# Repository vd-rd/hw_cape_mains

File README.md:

## Overview
 Isolated mains supply module designed to power IoT projects that have a <15W power requirement. It is designed around readily available step-down power modules with additional filtering to ensure compliance to standard specifications.

### Specifications

Two versions of the board are available, depending on the choice of the module:
 * MeanWell IRM 
 * Aimtec AMEOF 

In both cases the boards feature:
 * 85-240V input
 * 15W output at 12V
 * 5V regulated output using an LDO
 * Current sensor for measuring board consumption
 * IEC-C6 power connector
The board has a small footprint (80x40x25mm) with the power connector protruding an additional 3mm at the edge.

### Resources
You can find all necesary information to build or evaluate the module here:
   - [View layout and schematic](https://cadlab.io/project/) 
   - [View 3D board render](https://a360.co/2V6xbaF)
   - [Fabrication files](https://github.com/vd-rd/hw_cape_mains/releases)

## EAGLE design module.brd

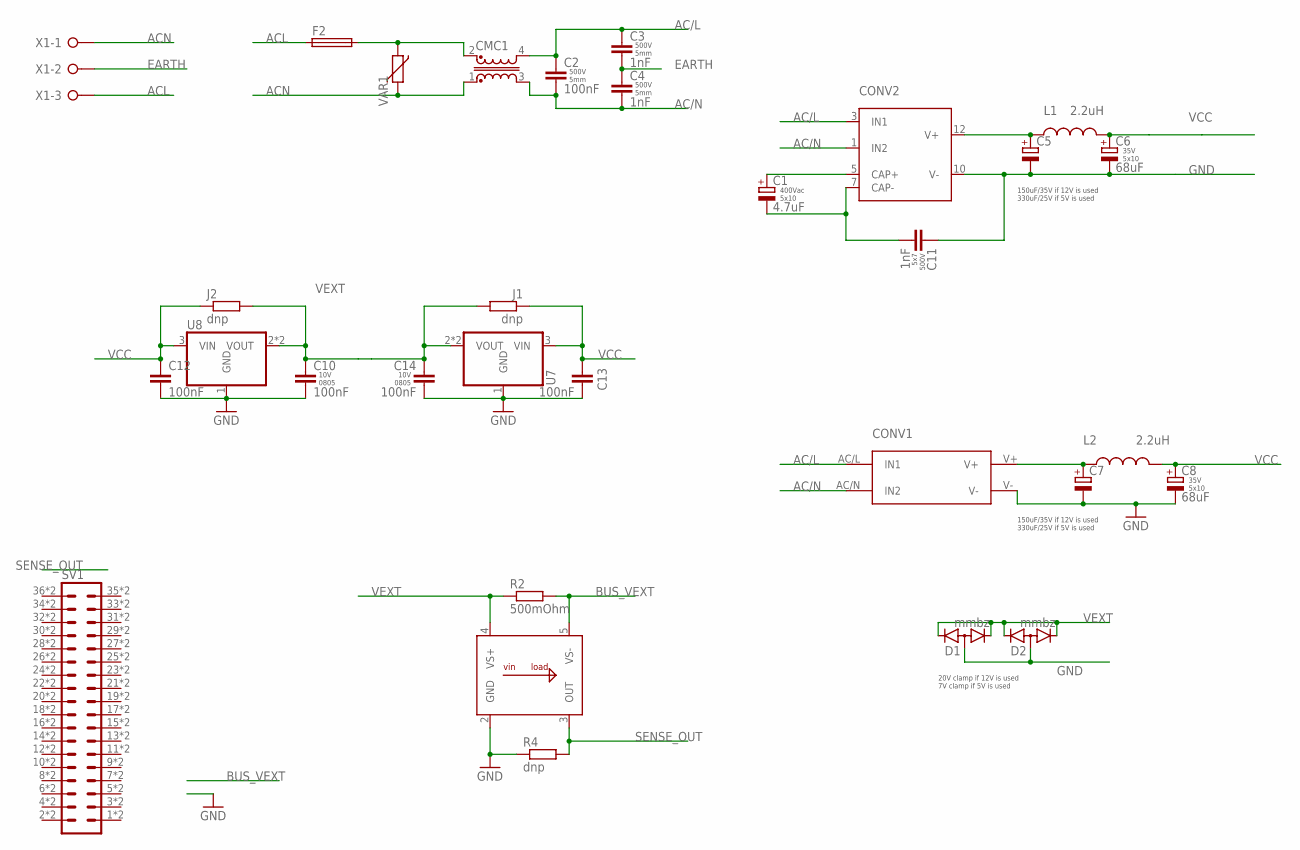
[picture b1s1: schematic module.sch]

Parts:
C1: 4.7uF; CAPPRD508W65D1000H1600B; RATING 400Vac
C2: 100nF; C050-025X075; RATING 500V
C3, C4: 1nF; C050-025X075; RATING 500V
C5, C7: CAP-POL-5PX10WX16H; CAPPRD508W65D1000H1600B
C6, C8: 68uF; CAPPRD508W65D1000H1600B; RATING 35V
C10, C12, C13, C14: 100nF; C0805
C11: 1nF; C050-025X075
CMC1: DLD-302U-1A; DLD
CONV1: IRM-03-12V; IRM-03
CONV2: AMEOF312SJZ; AMEOF3-JZ
D1, D2: mmbz; SOT23
F2: ZH8; ZH8X2
IC1: ZXCT1021; SOT95P240X110-5
J1, J2: dnp; R0805
L1, L2: 2.2uH; COIL0608
R2: 500mOhm; R0805
R4: dnp; R0603
SV1: MA18-2SMT; MA18-2-SMT
U7, U8: LD1117S50; SOT230P700X180-4
VAR1: S14K250; C7.5B4
X1: W237-03P; W237-133

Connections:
AC/L: C2.1, C3.1, CMC1.4, CONV1.AC/L (IN1), CONV2.3 (IN1)
AC/N: C2.2, C4.2, CMC1.3, CONV1.AC/N (IN2), CONV2.1 (IN2)
ACL: F2.1, F2.1A (1), X1.3
ACN: CMC1.1, VAR1.1, X1.1
BUS_VEXT: IC1.5 (VS-), R2.2
EARTH: C3.2, C4.1, X1.2
GND: C5.2 (-), C6.2 (-), C7.2 (-), C8.2 (-), C10.2, C11.1, C12.2, C13.2, C14.2, CONV1.V-, CONV2.10 (V-), D1.3 (A), D2.3 (A), IC1.2 (GND), R4.1, U7.1 (GND), U8.1 (GND)
unnamed: C1.1 (+), CONV2.5 (CAP+)
unnamed: C1.2 (-), C11.2, CONV2.7 (CAP-)
unnamed: C5.1 (+), CONV2.12 (V+), L1.P$1 (1)
unnamed: CMC1.2, F2.2, F2.2A (2), VAR1.2
unnamed: C7.1 (+), CONV1.V+, L2.P$1 (1)
SENSE_OUT: IC1.3 (OUT), R4.2
VCC: C6.1 (+), C8.1 (+), C12.1, C13.1, J1.1, J2.1, L1.P$2 (2), L2.P$2 (2), U7.3 (VIN), U8.3 (VIN)
VEXT: C10.1, C14.1, D1.1 (K1), D1.2 (K2), D2.1 (K1), D2.2 (K2), IC1.4 (VS+), J1.2, J2.2, R2.1, U7.2 (VOUT), U7.4 (VOUT), U8.2 (VOUT), U8.4 (VOUT)

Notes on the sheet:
150uF/35V if 12V is used 330uF/25V if 5V is used
20V clamp if 12V is used 7V clamp if 5V is used

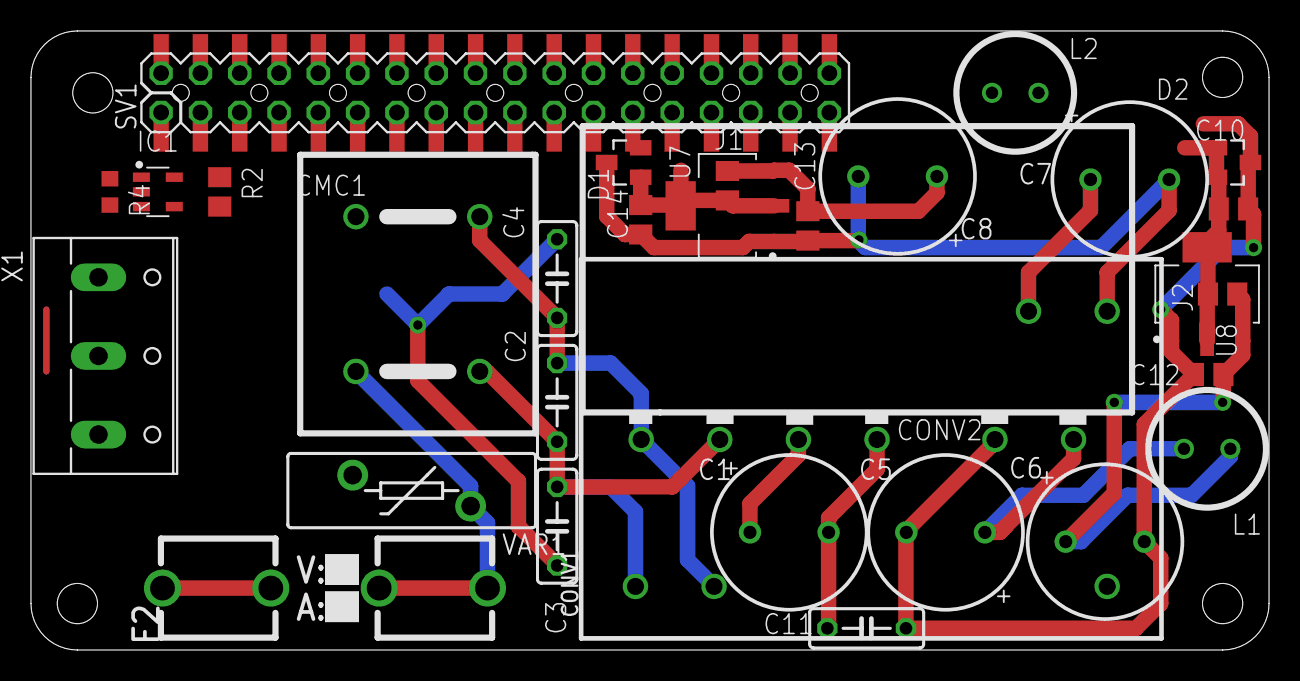
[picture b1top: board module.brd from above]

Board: 2 copper layers, 80.0 x 40.0 mm, 31 parts (0 on the bottom side), 15 nets.

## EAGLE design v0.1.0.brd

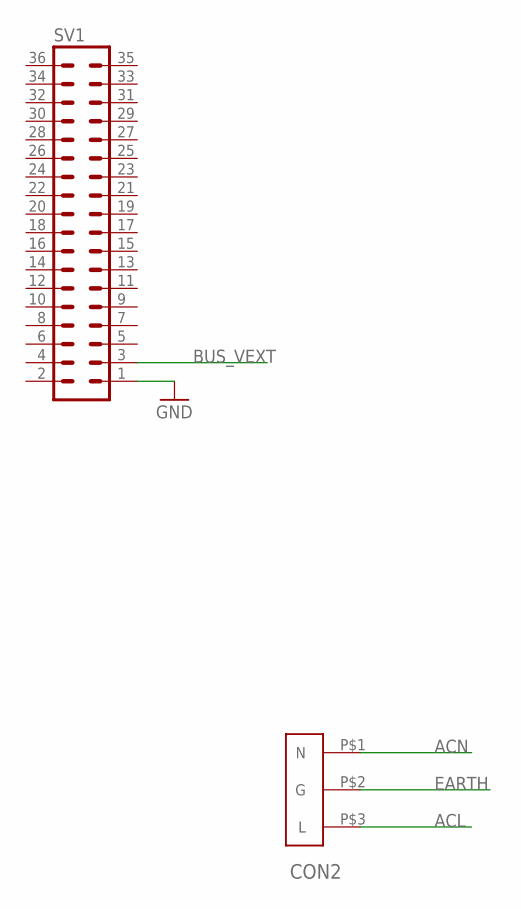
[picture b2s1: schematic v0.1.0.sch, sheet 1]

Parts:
CON2: 4300.0101; IEC-C6
SV1: MA18-2

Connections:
ACL: CON2.P$3 (L); also elsewhere on the board
ACN: CON2.P$1 (N); also elsewhere on the board
BUS_VEXT: SV1.3; also elsewhere on the board
EARTH: CON2.P$2 (G); also elsewhere on the board
GND: SV1.1; also elsewhere on the board

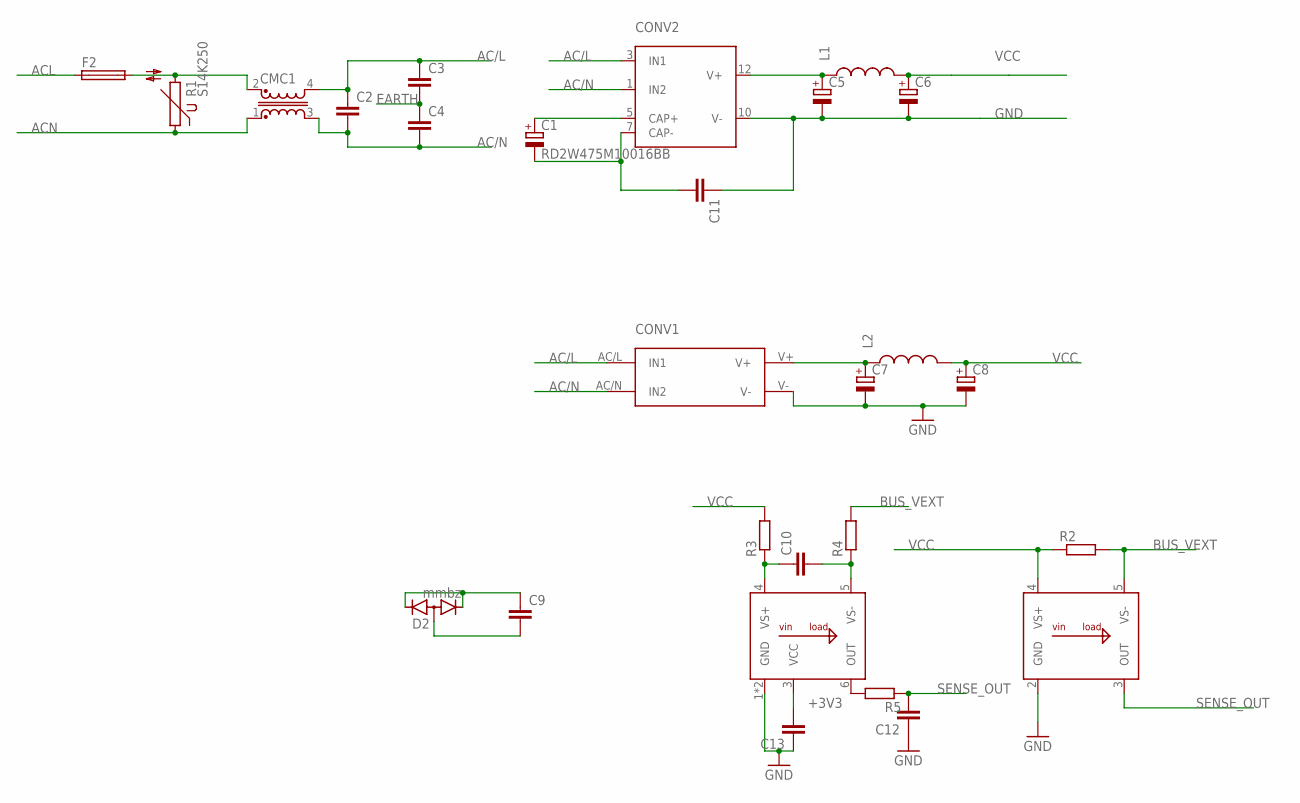
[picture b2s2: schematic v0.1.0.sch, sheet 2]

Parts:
C1: RD2W475M10016BB; E5-10,5
C2, C3, C4, C9, C11: C-EUC1206; C1206
C5, C6, C7, C8: CPOL-EUE5-10.5; E5-10,5
C10, C12, C13: C-EUC0402; C0402
CMC1: DLD-302U-1A; DLD
CONV1: IRM-03-12V; IRM-03
CONV2: AMEOF312SJZ; AMEOF3-JZ
D2: mmbz; SOT23
F2: ZH8; ZH8X2
IC1: ZXCT1021; SOT95P240X110-5
IC2: BQ500100; SC70-6
L1, L2: COIL0608-0.022; COIL0608
R1: S14K250
R2: R-EU_R0805; R0805
R3, R4, R5: R-EU_R0402; R0402

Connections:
+3V3: C13.2, IC2.3 (VCC)
AC/L: C2.1, C3.1, CMC1.4, CONV1.AC/L (IN1), CONV2.3 (IN1)
AC/N: C2.2, C4.2, CMC1.3, CONV1.AC/N (IN2), CONV2.1 (IN2)
ACL: F2.1, F2.1A (1); also elsewhere on the board
ACN: CMC1.1, R1.1; also elsewhere on the board
BUS_VEXT: IC1.5 (VS-), R2.2, R4.2; also elsewhere on the board
EARTH: C3.2, C4.1; also elsewhere on the board
GND: C5.-, C6.-, C7.-, C8.-, C11.1, C12.1, C13.1, CONV1.V-, CONV2.10 (V-), IC1.2 (GND), IC2.1 (GND), IC2.2 (GND); also elsewhere on the board
unnamed: C1.+, CONV2.5 (CAP+)
unnamed: C1.-, C11.2, CONV2.7 (CAP-)
unnamed: C5.+, CONV2.12 (V+), L1.P$1 (1)
unnamed: CMC1.2, F2.2, F2.2A (2), R1.2
unnamed: C7.+, CONV1.V+, L2.P$1 (1)
unnamed: C9.1, D2.1 (K1), D2.2 (K2)
unnamed: C9.2, D2.3 (A)
unnamed: IC2.6 (OUT), R5.2
unnamed: C10.1, IC2.4 (VS+), R3.1
unnamed: C10.2, IC2.5 (VS-), R4.1
SENSE_OUT: C12.2, IC1.3 (OUT), R5.1
VCC: C6.+, C8.+, IC1.4 (VS+), L1.P$2 (2), L2.P$2 (2), R2.1, R3.2

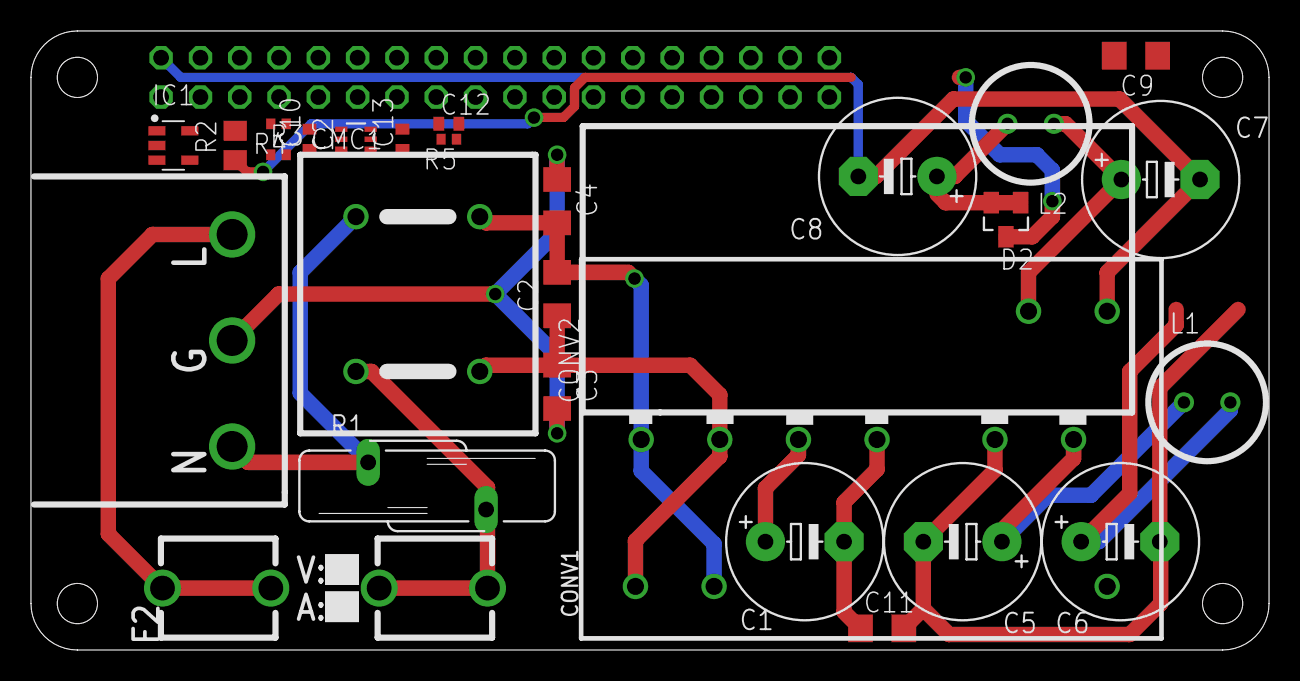
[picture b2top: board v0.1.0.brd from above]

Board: 2 copper layers, 80.0 x 40.0 mm, 29 parts (1 on the bottom side), 20 nets.

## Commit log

2018-12-26 board bringup
2019-01-17 added assembly variants
2019-01-17 added documentation
2019-01-17 defined connections
2019-01-17 polished schematic
2019-01-17 added identification prints
2019-01-17 added logo
2019-01-17 minor fixes
2019-03-12 cosmetic fixes
2019-05-02 project: update structure
2019-05-02 layout: minor routing changes
2019-09-23 project: README cosmetic fixes
2019-09-23 project: remove logo and add new connector
2019-09-23 project: add new connector for embedded apps
